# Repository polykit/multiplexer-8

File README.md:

# Polykit Multiplexer 16:8

This repository contains schematics and PCB layout of a 2x8 to 8 channel multiplexer. It can be used to switch between different waveforms of a polyphonic oscillator. It is based on four 4066 bilateral switches and can handle a 10Vpp signal. It is powered by +-12V Eurorack style power supply.

## References

https://www.ti.com/lit/ds/symlink/cd4066b.pdf

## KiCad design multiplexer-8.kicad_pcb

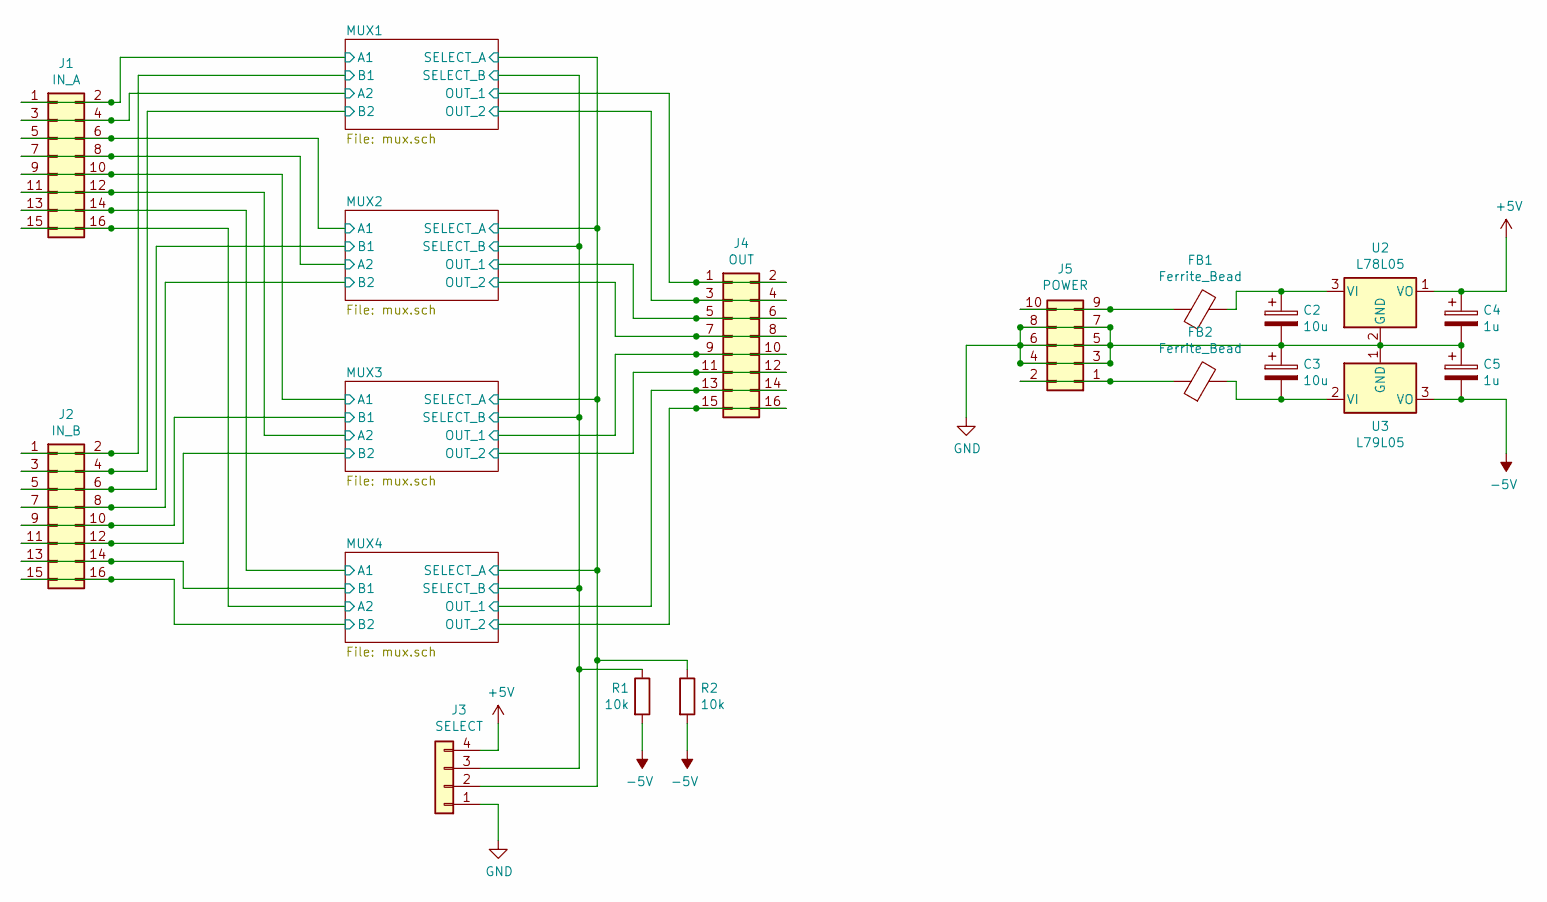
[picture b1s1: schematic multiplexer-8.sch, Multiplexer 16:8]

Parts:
C2, C3: 10u; CP_Radial_D5.0mm_P2.50mm
C4, C5: 1u; CP_Radial_D5.0mm_P2.50mm
FB1, FB2: Ferrite_Bead; R_Axial_DIN0207_L6.3mm_D2.5mm_P10.16mm_Horizontal
J1: IN_A; IDC-Header_2x08_P2.54mm_Vertical
J2: IN_B; IDC-Header_2x08_P2.54mm_Vertical
J3: SELECT; Molex_KK-254_AE-6410-04A_1x04_P2.54mm_Vertical
J4: OUT; IDC-Header_2x08_P2.54mm_Vertical
J5: POWER; IDC-Header_2x05_P2.54mm_Vertical
R1, R2: 10k; R_Axial_DIN0207_L6.3mm_D2.5mm_P10.16mm_Horizontal
U2: L78L05; TO-92_Inline_Wide
U3: L79L05; TO-92_Inline_Wide

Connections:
+5V: C4.1, J3.4, U2.1 (VO); also elsewhere on the board
-5V: C5.2, R1.2, R2.2, U3.3 (VO); also elsewhere on the board
/MUX1/A1: J1.1, J1.2; also elsewhere on the board
/MUX1/A2: J1.3, J1.4; also elsewhere on the board
/MUX1/B1: J2.1, J2.2; also elsewhere on the board
/MUX1/B2: J2.3, J2.4; also elsewhere on the board
/MUX1/OUT_1: J4.1, J4.2; also elsewhere on the board
/MUX1/OUT_2: J4.3, J4.4; also elsewhere on the board
/MUX1/SELECT_A: J3.2, R2.1; also elsewhere on the board
/MUX1/SELECT_B: J3.3, R1.1; also elsewhere on the board
/MUX2/A1: J1.5, J1.6; also elsewhere on the board
/MUX2/A2: J1.7, J1.8; also elsewhere on the board
/MUX2/B1: J2.5, J2.6; also elsewhere on the board
/MUX2/B2: J2.7, J2.8; also elsewhere on the board
/MUX2/OUT_1: J4.5, J4.6; also elsewhere on the board
/MUX2/OUT_2: J4.7, J4.8; also elsewhere on the board
/MUX3/A1: J1.9, J1.10; also elsewhere on the board
/MUX3/A2: J1.11, J1.12; also elsewhere on the board
/MUX3/B1: J2.9, J2.10; also elsewhere on the board
/MUX3/B2: J2.11, J2.12; also elsewhere on the board
/MUX3/OUT_1: J4.9, J4.10; also elsewhere on the board
/MUX3/OUT_2: J4.11, J4.12; also elsewhere on the board
/MUX4/A1: J1.13, J1.14; also elsewhere on the board
/MUX4/A2: J1.15, J1.16; also elsewhere on the board
/MUX4/B1: J2.13, J2.14; also elsewhere on the board
/MUX4/B2: J2.15, J2.16; also elsewhere on the board
/MUX4/OUT_1: J4.13, J4.14; also elsewhere on the board
/MUX4/OUT_2: J4.15, J4.16; also elsewhere on the board
GND: C2.2, C3.1, C4.2, C5.1, J3.1, J5.3, J5.4, J5.5, J5.6, J5.7, J5.8, U2.2 (GND), U3.1 (GND)
unnamed: C2.1, FB1.2, U2.3 (VI)
unnamed: C3.2, FB2.2, U3.2 (VI)
unnamed: FB1.1, J5.9, J5.10
unnamed: FB2.1, J5.1, J5.2

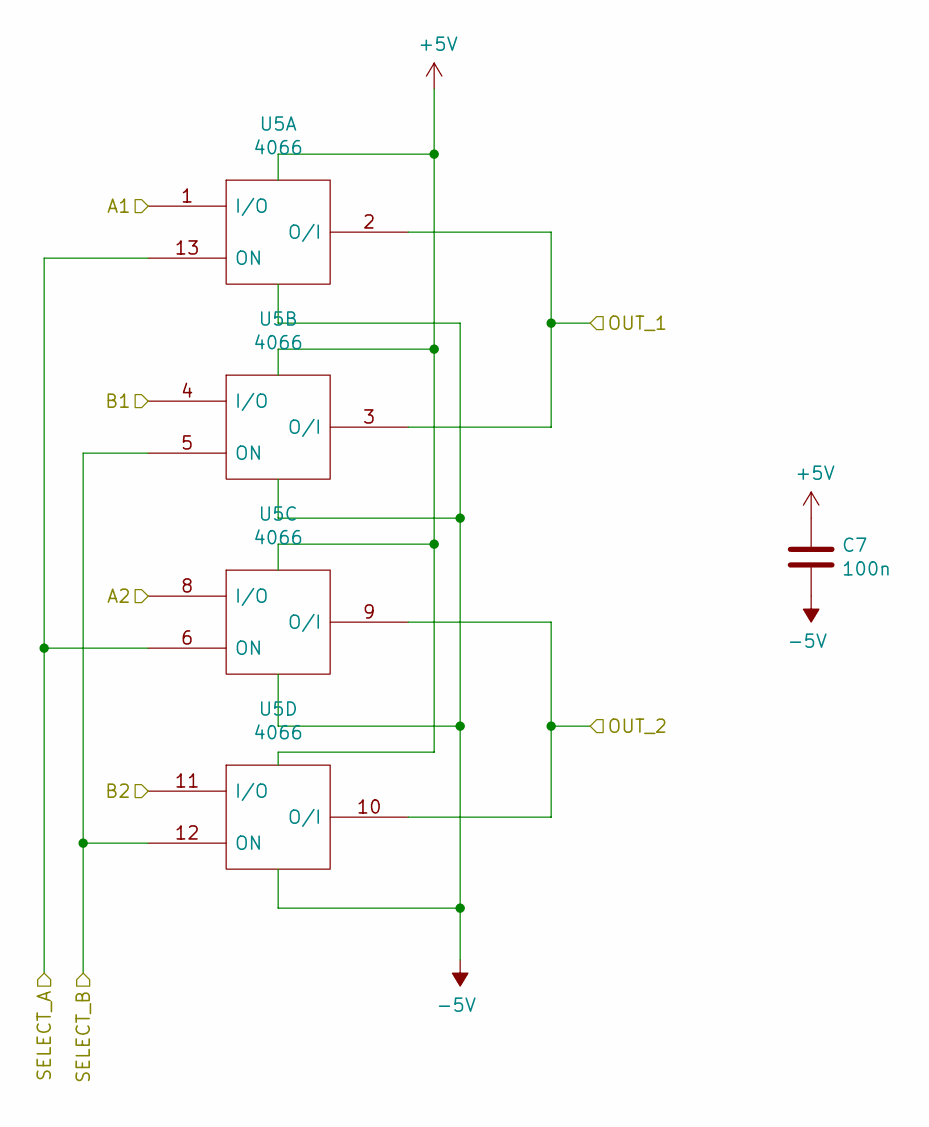
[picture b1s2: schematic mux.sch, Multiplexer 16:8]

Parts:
C1: 100n; C_Disc_D5.0mm_W2.5mm_P5.00mm
U1: 4066; DIP-14_W7.62mm_Socket_LongPads

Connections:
+5V: C1.1, U1.14 (Vdd); also elsewhere on the board
-5V: C1.2, U1.7 (Vss); also elsewhere on the board
/MUX1/A1: U1.1 (I/O); also elsewhere on the board
/MUX1/A2: U1.8 (I/O); also elsewhere on the board
/MUX1/B1: U1.4 (I/O); also elsewhere on the board
/MUX1/B2: U1.11 (I/O); also elsewhere on the board
/MUX1/OUT_1: U1.2 (O/I), U1.3 (O/I); also elsewhere on the board
/MUX1/OUT_2: U1.9 (O/I), U1.10 (O/I); also elsewhere on the board
/MUX1/SELECT_A: U1.6 (ON), U1.13 (ON); also elsewhere on the board
/MUX1/SELECT_B: U1.5 (ON), U1.12 (ON); also elsewhere on the board

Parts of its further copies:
C6, C7, C8: 100n; C_Disc_D5.0mm_W2.5mm_P5.00mm
U4, U5, U6: 4066; DIP-14_W7.62mm_Socket_LongPads

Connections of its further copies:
+5V: C6.1, C7.1, C8.1, U4.14 (Vdd), U5.14 (Vdd), U6.14 (Vdd); also elsewhere on the board
-5V: C6.2, C7.2, C8.2, U4.7 (Vss), U5.7 (Vss), U6.7 (Vss); also elsewhere on the board
/MUX1/SELECT_A: U4.6 (ON), U4.13 (ON), U5.6 (ON), U5.13 (ON), U6.6 (ON), U6.13 (ON); also elsewhere on the board
/MUX1/SELECT_B: U4.5 (ON), U4.12 (ON), U5.5 (ON), U5.12 (ON), U6.5 (ON), U6.12 (ON); also elsewhere on the board
/MUX2/A1: U4.1 (I/O); also elsewhere on the board
/MUX2/A2: U4.8 (I/O); also elsewhere on the board
/MUX2/B1: U4.4 (I/O); also elsewhere on the board
/MUX2/B2: U4.11 (I/O); also elsewhere on the board
/MUX2/OUT_1: U4.2 (O/I), U4.3 (O/I); also elsewhere on the board
/MUX2/OUT_2: U4.9 (O/I), U4.10 (O/I); also elsewhere on the board
/MUX3/A1: U5.1 (I/O); also elsewhere on the board
/MUX3/A2: U5.8 (I/O); also elsewhere on the board
/MUX3/B1: U5.4 (I/O); also elsewhere on the board
/MUX3/B2: U5.11 (I/O); also elsewhere on the board
/MUX3/OUT_1: U5.2 (O/I), U5.3 (O/I); also elsewhere on the board
/MUX3/OUT_2: U5.9 (O/I), U5.10 (O/I); also elsewhere on the board
/MUX4/A1: U6.1 (I/O); also elsewhere on the board
/MUX4/A2: U6.8 (I/O); also elsewhere on the board
/MUX4/B1: U6.4 (I/O); also elsewhere on the board
/MUX4/B2: U6.11 (I/O); also elsewhere on the board
/MUX4/OUT_1: U6.2 (O/I), U6.3 (O/I); also elsewhere on the board
/MUX4/OUT_2: U6.9 (O/I), U6.10 (O/I); also elsewhere on the board

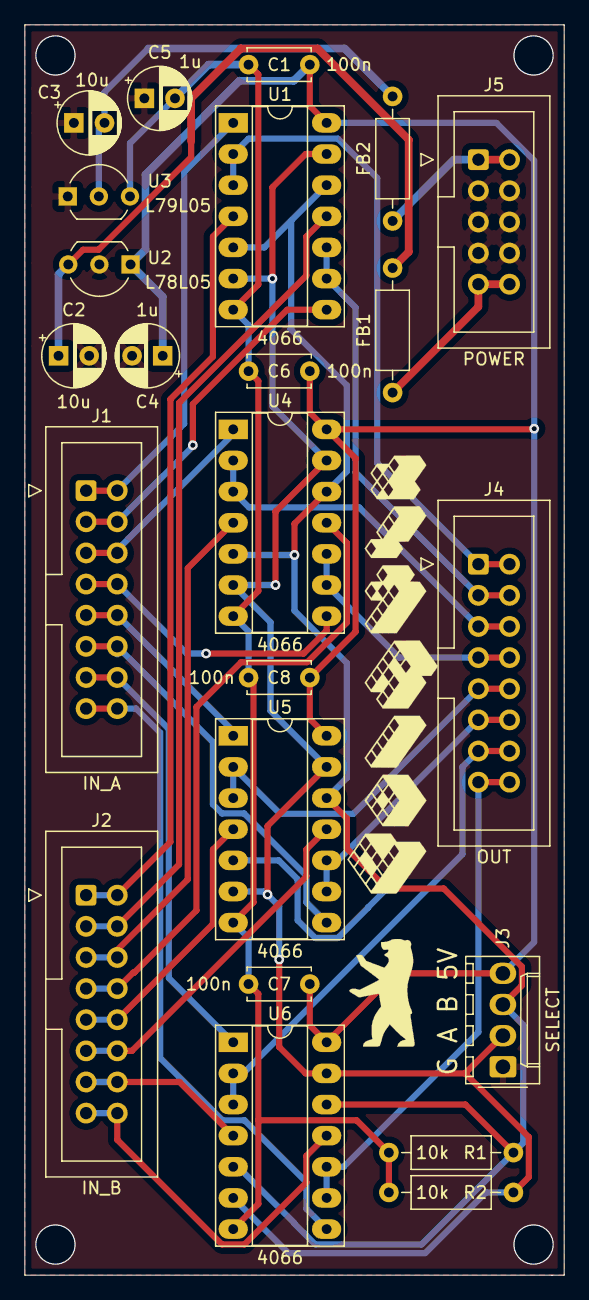
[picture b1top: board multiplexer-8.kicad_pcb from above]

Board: 2 copper layers, 44.0 x 102.0 mm, 23 parts (0 on the bottom side), 33 nets.

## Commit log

2021-06-30 Initial import
2021-06-30 Add readme
